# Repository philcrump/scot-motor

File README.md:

# scot-motor

Motor Interface for the SCOT.

* 9-36V DC Input
* STM32F042K6 Microcontroller @ 48MHz
* MCP2562 CAN 2.0A/B Communication Interface
* DRV8872 3.6A PWM H-Bridge Motor Driver
* INA260 Motor Voltage & Current Supply Monitoring
* NCV8450 800mA Clutch Driver
* E-Stop, End-of-travel Limit Interlocks support
  * Hardware CMOS NAND Logic (immune to software override)
  * Opto-isolation of Switches from Logic Inputs (power supply not isolated)

[**Circuit Board Schematic**](https://github.com/philcrump/scot-motor/raw/master/scot-motor-schematic.pdf)

## PCB (CAD Render)

### Errata - April 2020

* ~~0603 footprint used for C3 (4.7uF, 25V), should be 0805 - Minimal impact, 0805 still fits.~~ - Fixed in August 2020.

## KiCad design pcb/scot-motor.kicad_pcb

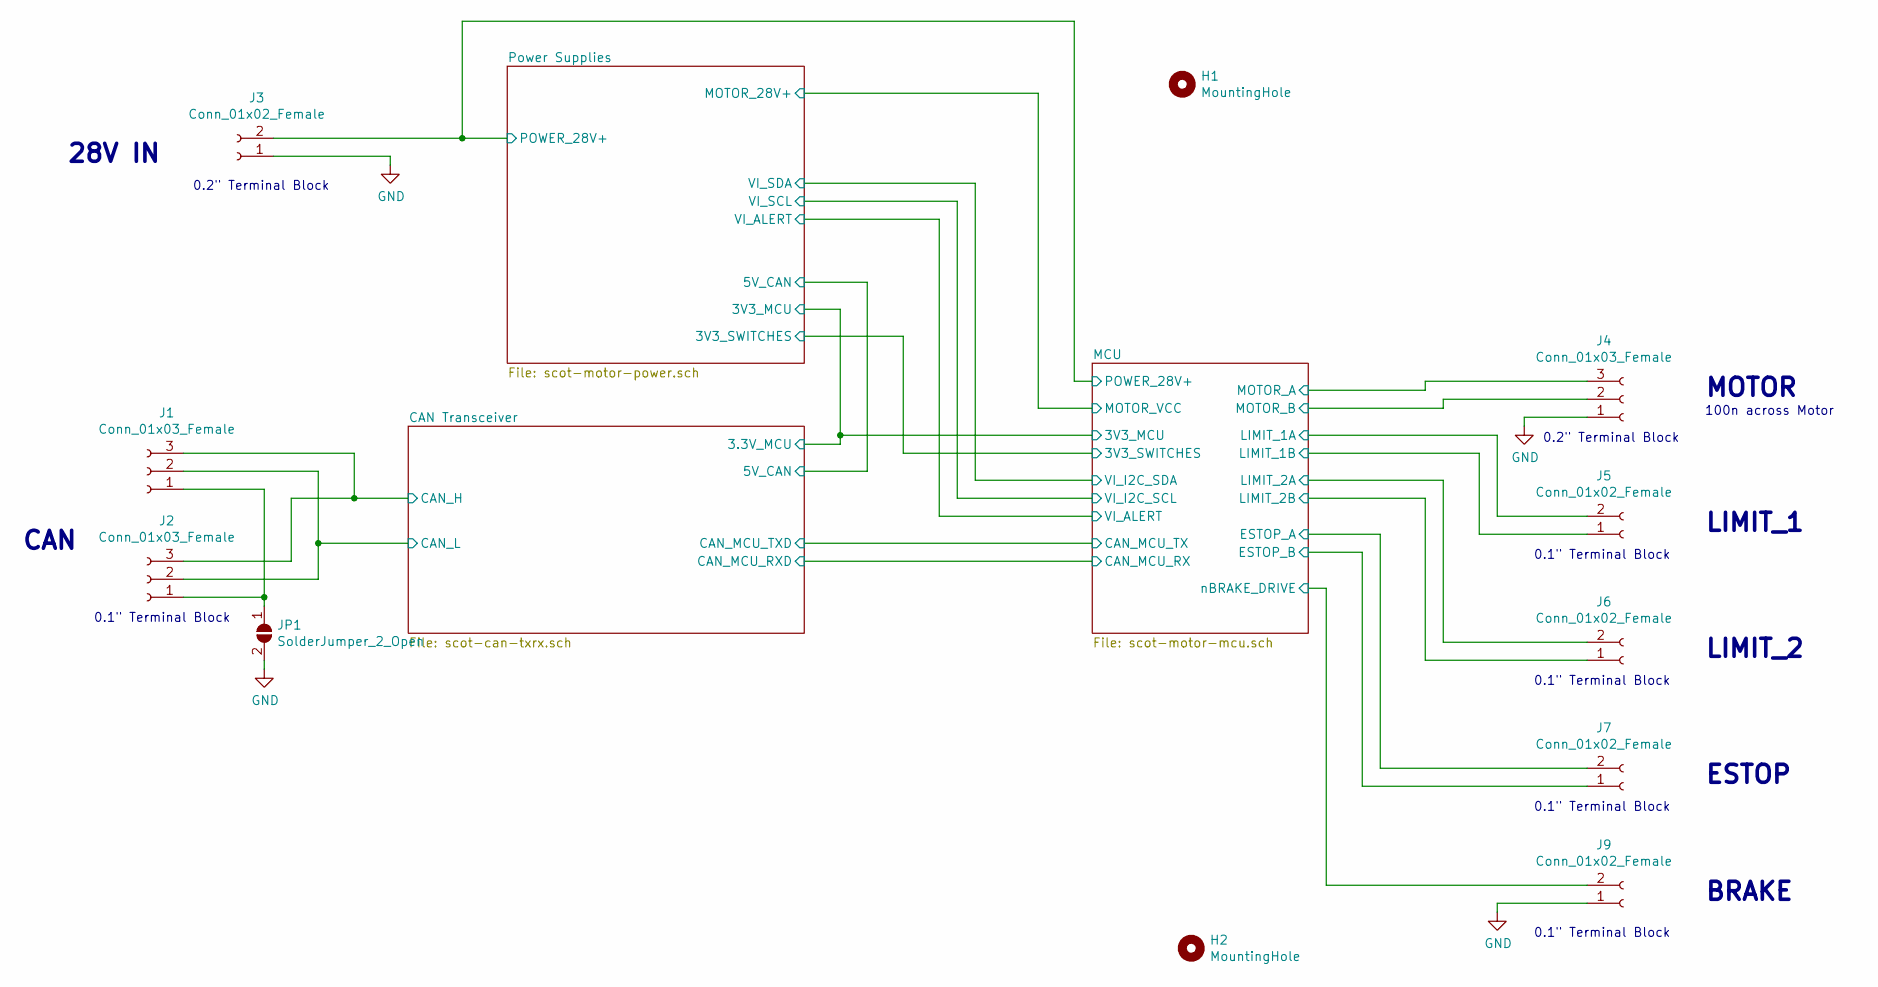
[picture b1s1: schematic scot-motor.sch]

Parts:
H1, H2: MountingHole; M3_MOUNT
J1, J2: Conn_01x03_Female; TerminalBlock_TE_282834-3_1x03_P2.54mm_Horizontal
J3: Conn_01x02_Female; TerminalBlock_RND_205-00287_1x02_P5.08mm_Horizontal
J4: Conn_01x03_Female; TerminalBlock_RND_205-00288_1x03_P5.08mm_Horizontal
J5, J6, J7, J9: Conn_01x02_Female; TerminalBlock_TE_282834-2_1x02_P2.54mm_Horizontal
JP1: SolderJumper_2_Open; SolderJumper-2_P1.3mm_Open_RoundedPad1.0x1.5mm

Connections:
/CAN Transceiver/CAN_H: J1.3, J2.3; also elsewhere on the board
/CAN Transceiver/CAN_L: J1.2, J2.2; also elsewhere on the board
/MCU/ESTOP_A: J7.2; also elsewhere on the board
/MCU/ESTOP_B: J7.1; also elsewhere on the board
/MCU/LIMIT_1A: J5.2; also elsewhere on the board
/MCU/LIMIT_1B: J5.1; also elsewhere on the board
/MCU/LIMIT_2A: J6.2; also elsewhere on the board
/MCU/LIMIT_2B: J6.1; also elsewhere on the board
/MCU/MOTOR_A: J4.3; also elsewhere on the board
/MCU/MOTOR_B: J4.2; also elsewhere on the board
/MCU/POWER_28V+: J3.2; also elsewhere on the board
/MCU/nBRAKE_DRIVE: J9.2; also elsewhere on the board
GND: J3.1, J4.1, J9.1, JP1.2 (B); also elsewhere on the board
unnamed: J1.1, J2.1, JP1.1 (A)

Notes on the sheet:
0.2" Terminal Block
0.1" Terminal Block
MOTOR
LIMIT_1
LIMIT_2
ESTOP
28V IN
CAN
100n across Motor
BRAKE

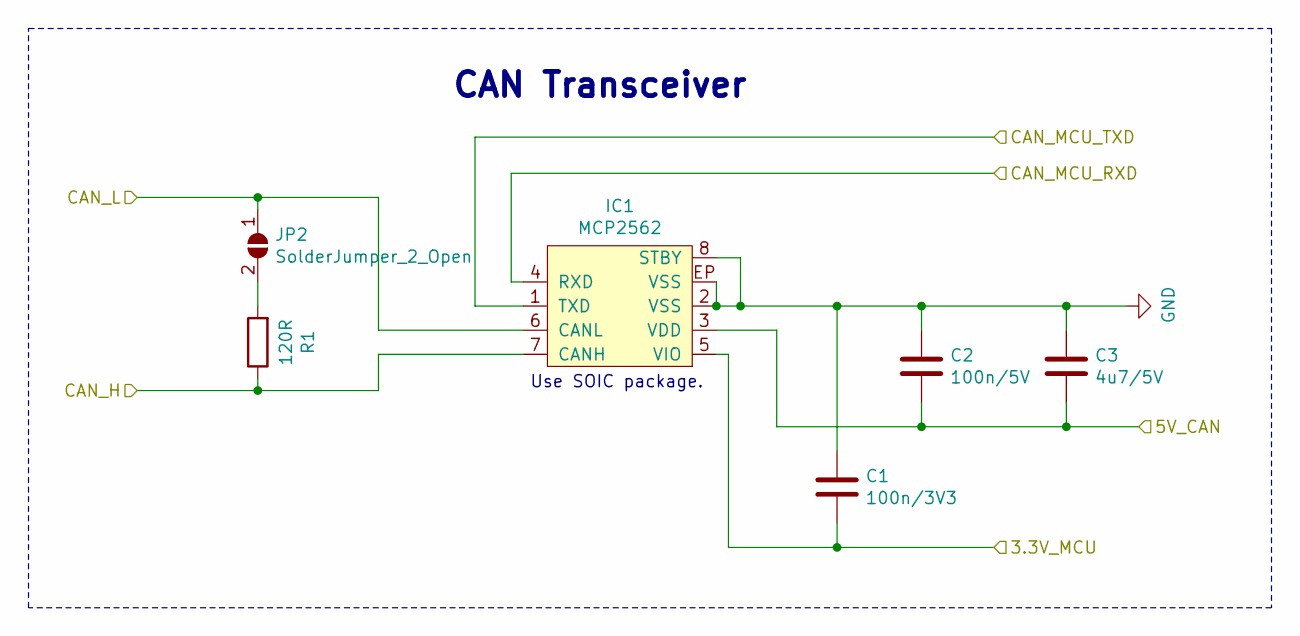
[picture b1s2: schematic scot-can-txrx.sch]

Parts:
C3: 4u7/5V; C_0805_2012Metric_Pad1.15x1.40mm_HandSolder
C53: 100n/3V3; C_0603_1608Metric_Pad1.05x0.95mm_HandSolder
C54: 100n/5V; C_0603_1608Metric_Pad1.05x0.95mm_HandSolder
IC1: MCP2562; SOIC-8-EP
JP2: SolderJumper_2_Open; SolderJumper-2_P1.3mm_Open_RoundedPad1.0x1.5mm
R36: 120R; R_0805_2012Metric_Pad1.15x1.40mm_HandSolder

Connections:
3v3: IC1.5 (VIO); also elsewhere on the board
/CAN Transceiver/5V_CAN: C3.2, IC1.3 (VDD); also elsewhere on the board
/CAN Transceiver/CAN_H: IC1.7 (CANH); also elsewhere on the board
/CAN Transceiver/CAN_L: IC1.6 (CANL), JP2.1 (A); also elsewhere on the board
/MCU/CAN_MCU_RX: IC1.4 (RXD); also elsewhere on the board
/MCU/CAN_MCU_TX: IC1.1 (TXD); also elsewhere on the board
GND: C3.1, IC1.2 (VSS), IC1.8 (STBY), IC1.EP (VSS); also elsewhere on the board
unnamed 57: JP2.2 (B); also elsewhere on the board

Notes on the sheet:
Use SOIC package.
CAN Transceiver

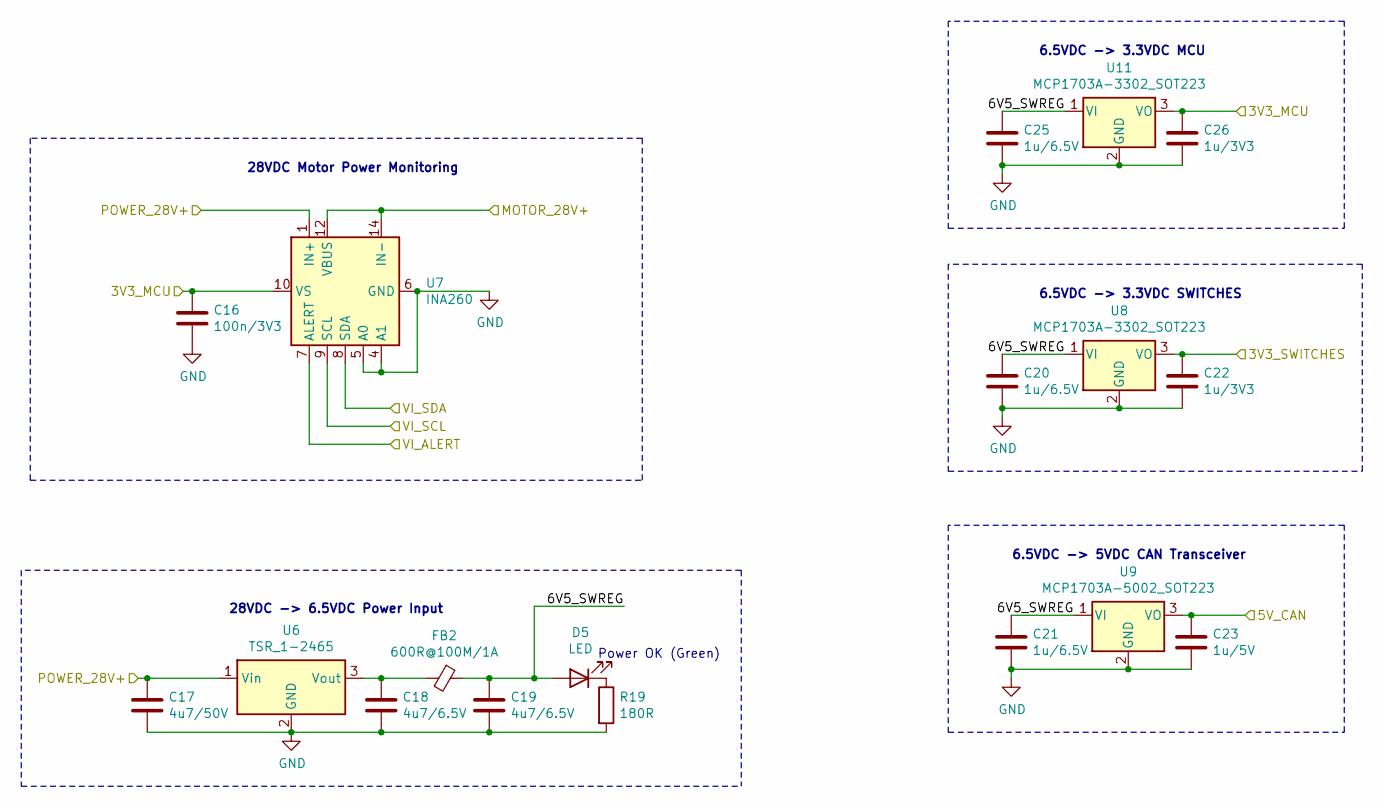
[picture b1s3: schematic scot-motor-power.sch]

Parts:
C16: 100n/3V3; C_0603_1608Metric_Pad1.05x0.95mm_HandSolder
C17: 4u7/50V; C_1206_3216Metric_Pad1.42x1.75mm_HandSolder
C18, C19: 4u7/6.5V; C_0805_2012Metric_Pad1.15x1.40mm_HandSolder
C20, C21, C25: 1u/6.5V; C_0603_1608Metric_Pad1.05x0.95mm_HandSolder
C22, C26: 1u/3V3; C_0603_1608Metric_Pad1.05x0.95mm_HandSolder
C23: 1u/5V; C_0603_1608Metric_Pad1.05x0.95mm_HandSolder
D5: LED; LED_1210_3225Metric_Pad1.42x2.65mm_HandSolder
FB2: 600R@100M/1A; L_0805_2012Metric_Pad1.15x1.40mm_HandSolder
R19: 180R; R_0805_2012Metric_Pad1.15x1.40mm_HandSolder
U6: TSR_1-2465; Converter_DCDC_TRACO_TSR-1_THT
U7: INA260; TSSOP-16_4.4x5mm_P0.65mm
U8, U11: MCP1703A-3302_SOT223; SOT-223-3_TabPin2
U9: MCP1703A-5002_SOT223; SOT-223-3_TabPin2

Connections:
3v3: C16.1, C26.1, U7.10 (VS), U11.3 (VO); also elsewhere on the board
+3.3VP: C22.1, U8.3 (VO); also elsewhere on the board
/CAN Transceiver/5V_CAN: C23.1, U9.3 (VO); also elsewhere on the board
/MCU/POWER_28V+: C17.1, U6.1 (Vin), U7.1 (IN+), U7.2 (IN+), U7.3 (IN+); also elsewhere on the board
/MCU/VI_ALERT: U7.7 (ALERT); also elsewhere on the board
/MCU/VI_I2C_SCL: U7.9 (SCL); also elsewhere on the board
/MCU/VI_I2C_SDA: U7.8 (SDA); also elsewhere on the board
/Power Supplies/6V5_SWREG: C19.1, C20.1, C21.1, C25.1, D5.2 (A), FB2.1, U8.1 (VI), U9.1 (VI), U11.1 (VI)
/Power Supplies/MOTOR_28V+: U7.12 (VBUS), U7.14 (IN-), U7.15 (IN-), U7.16 (IN-); also elsewhere on the board
GND: C16.2, C17.2, C18.2, C19.2, C20.2, C21.2, C22.2, C23.2, C25.2, C26.2, R19.2, U6.2 (GND), U7.4 (A1), U7.5 (A0), U7.6 (GND), U7.11 (GND), U8.2 (GND), U9.2 (GND), U11.2 (GND); also elsewhere on the board
unnamed: C18.1, FB2.2, U6.3 (Vout)
unnamed: D5.1 (K), R19.1

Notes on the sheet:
6.5VDC -> 5VDC CAN Transceiver
6.5VDC -> 3.3VDC SWITCHES
28VDC -> 6.5VDC Power Input
28VDC Motor Power Monitoring
Power OK (Green)
6.5VDC -> 3.3VDC MCU

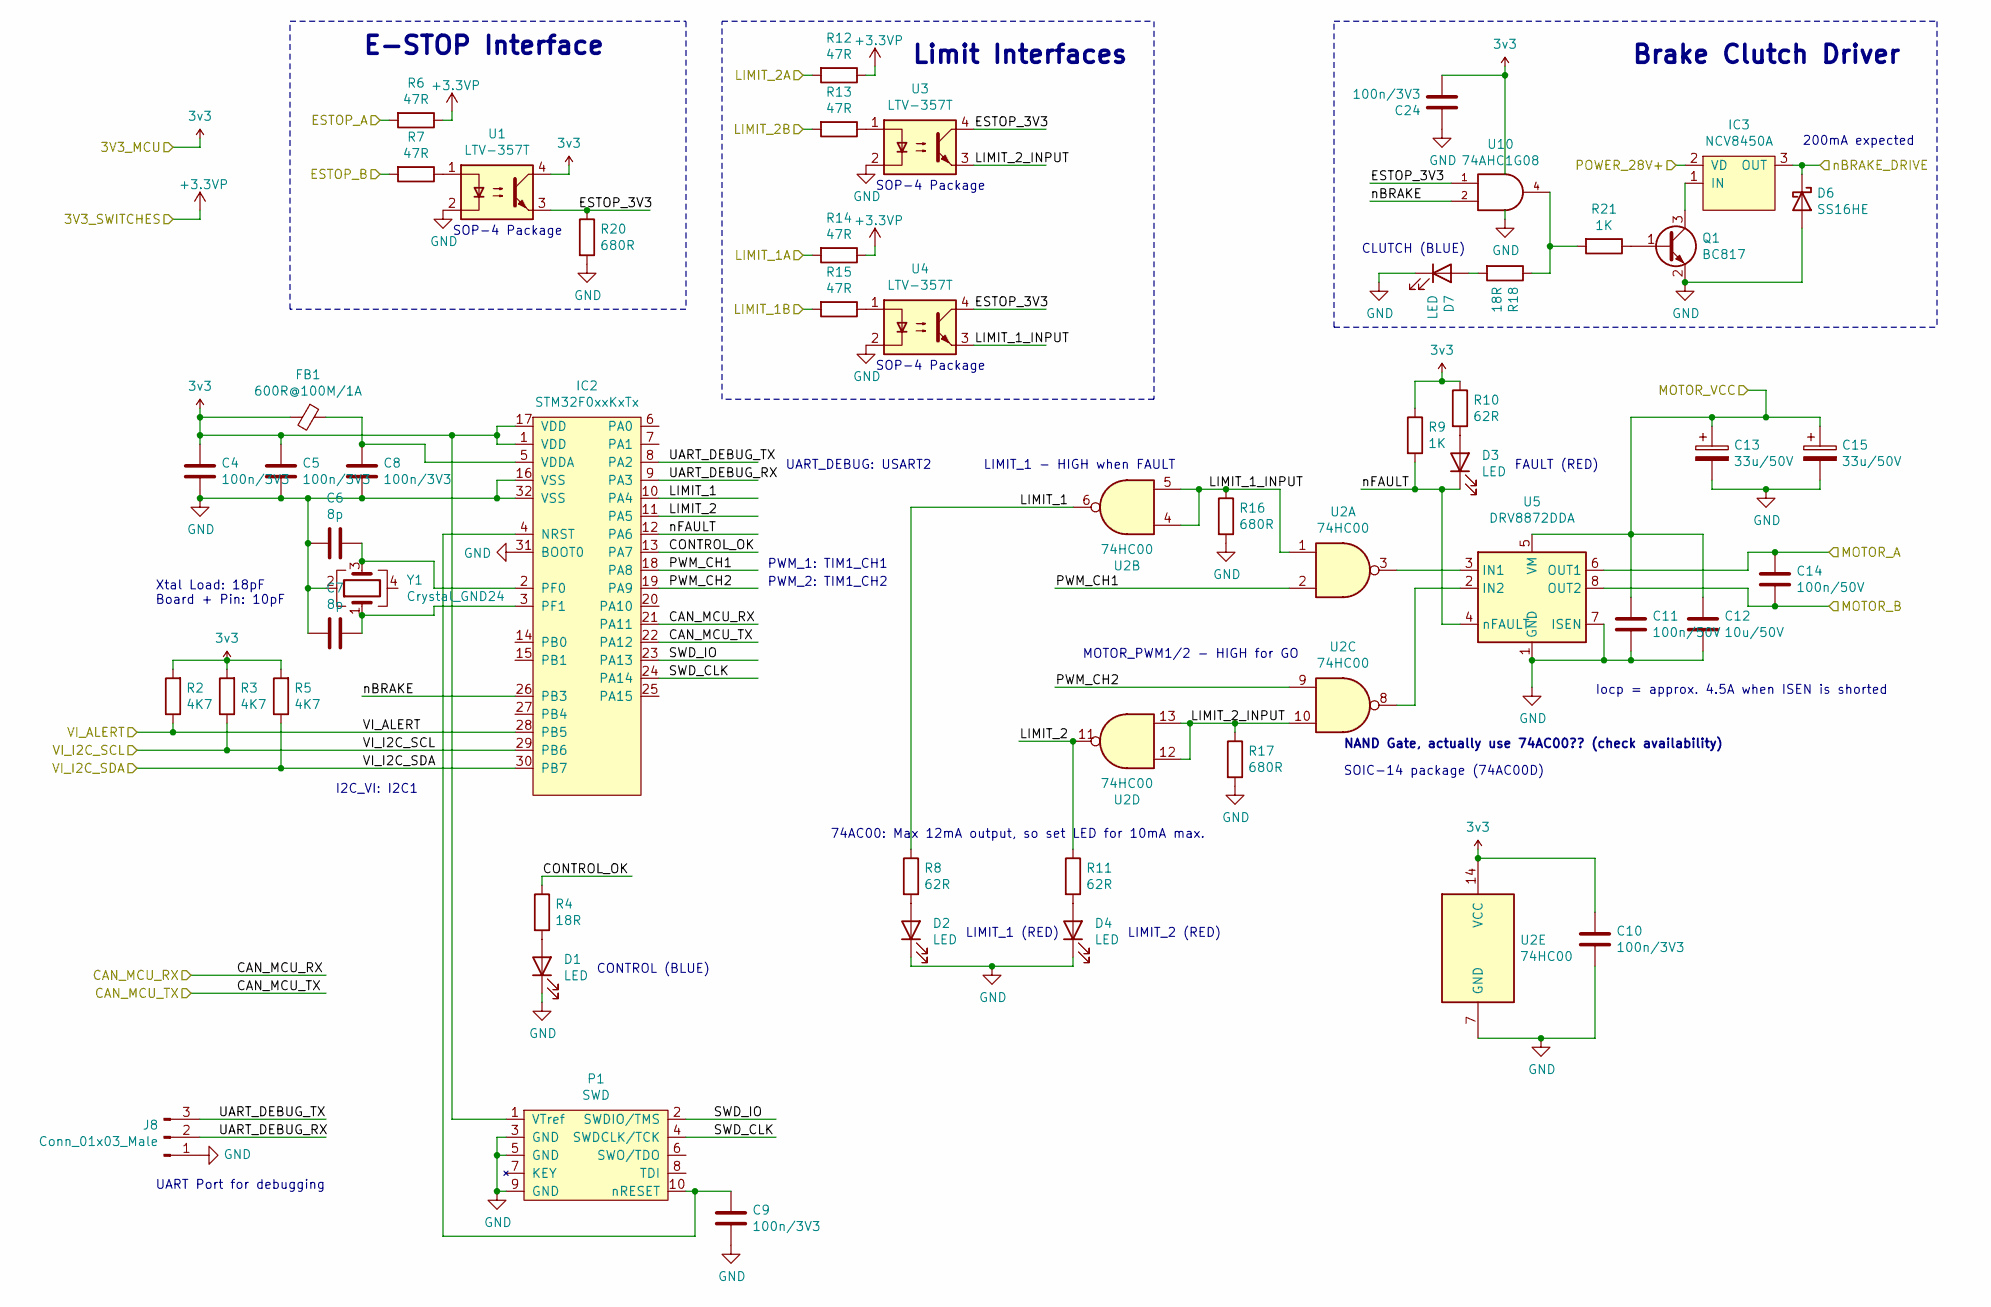
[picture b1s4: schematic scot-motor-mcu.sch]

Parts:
C4, C5, C8, C9, C10, C24: 100n/3V3; C_0603_1608Metric_Pad1.05x0.95mm_HandSolder
C6, C7: 8p; C_0603_1608Metric_Pad1.05x0.95mm_HandSolder
C11, C14: 100n/50V; C_0603_1608Metric_Pad1.05x0.95mm_HandSolder
C12: 10u/50V; C_1210_3225Metric_Pad1.42x2.65mm_HandSolder
C13, C15: 33u/50V; CP_Elec_8x10.5
D1, D2, D3, D4, D7: LED; LED_1210_3225Metric_Pad1.42x2.65mm_HandSolder
D6: SS16HE; SOD-323
FB1: 600R@100M/1A; L_0805_2012Metric_Pad1.15x1.40mm_HandSolder
IC2: STM32F0xxKxTx; LQFP-32; Farnell 2432085
IC3: NCV8450A; SOT-223-3_TabPin2; Mouser 863-NCV8450ASTT3G
J8: Conn_01x03_Male; PinHeader_1x03_P2.54mm_Vertical
P1: SWD; FTSH-105-01-F-D-K
Q1: BC817; SOT-23
R2, R3, R5: 4K7; R_0603_1608Metric_Pad1.05x0.95mm_HandSolder
R4, R18: 18R; R_0805_2012Metric_Pad1.15x1.40mm_HandSolder
R6, R7, R12, R13, R14, R15: 47R; R_0805_2012Metric_Pad1.15x1.40mm_HandSolder
R8, R10, R11: 62R; R_0805_2012Metric_Pad1.15x1.40mm_HandSolder
R9, R21: 1K; R_0603_1608Metric_Pad1.05x0.95mm_HandSolder
R16, R17, R20: 680R; R_0603_1608Metric_Pad1.05x0.95mm_HandSolder
U1, U3, U4: LTV-357T; SO-4_4.4x3.6mm_P2.54mm
U2: 74HC00; SOIC-14
U5: DRV8872DDA; Texas_HTSOP-8-1EP_3.9x4.9mm_P1.27mm_EP2.95x4.9mm_Mask2.4x3.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
U10: 74AHC1G08; SOT-23-5
Y1: Crystal_GND24; Crystal_SMD_Abracon_ABM8G-4Pin_3.2x2.5mm

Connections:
3v3: C4.1, C5.1, C10.1, C24.2, FB1.2, IC2.1 (VDD), IC2.17 (VDD), P1.1 (VTref), R2.2, R3.2, R5.2, R9.1, R10.1, U1.4, U2.14 (VCC), U10.5 (VCC); also elsewhere on the board
+3.3VP: R6.1, R12.1, R14.1; also elsewhere on the board
/MCU/CAN_MCU_RX: IC2.21 (PA11); also elsewhere on the board
/MCU/CAN_MCU_TX: IC2.22 (PA12); also elsewhere on the board
/MCU/CONTROL_OK: IC2.13 (PA7), R4.1
/MCU/ESTOP_3V3: R20.1, U1.3, U3.4, U4.4, U10.1
/MCU/ESTOP_A: R6.2; also elsewhere on the board
/MCU/ESTOP_B: R7.2; also elsewhere on the board
/MCU/LIMIT_1: IC2.10 (PA4), R8.1, U2.6
/MCU/LIMIT_1A: R14.2; also elsewhere on the board
/MCU/LIMIT_1B: R15.2; also elsewhere on the board
/MCU/LIMIT_1_INPUT: R16.1, U2.1, U2.4, U2.5, U4.3
/MCU/LIMIT_2: IC2.11 (PA5), R11.1, U2.11
/MCU/LIMIT_2A: R12.2; also elsewhere on the board
/MCU/LIMIT_2B: R13.2; also elsewhere on the board
/MCU/LIMIT_2_INPUT: R17.1, U2.10, U2.12, U2.13, U3.3
/MCU/MOTOR_A: C14.1, U5.6 (OUT1); also elsewhere on the board
/MCU/MOTOR_B: C14.2, U5.8 (OUT2); also elsewhere on the board
/MCU/POWER_28V+: IC3.2 (VD); also elsewhere on the board
/MCU/PWM_CH1: IC2.18 (PA8), U2.2
/MCU/PWM_CH2: IC2.19 (PA9), U2.9
/MCU/SWD_CLK: IC2.24 (PA14), P1.4 (SWDCLK/TCK)
/MCU/SWD_IO: IC2.23 (PA13), P1.2 (SWDIO/TMS)
/MCU/UART_DEBUG_RX: IC2.9 (PA3), J8.2
/MCU/UART_DEBUG_TX: IC2.8 (PA2), J8.3
/MCU/VI_ALERT: IC2.28 (PB5), R2.1; also elsewhere on the board
/MCU/VI_I2C_SCL: IC2.29 (PB6), R3.1; also elsewhere on the board
/MCU/VI_I2C_SDA: IC2.30 (PB7), R5.1; also elsewhere on the board
/MCU/nBRAKE: IC2.26 (PB3), U10.2
/MCU/nBRAKE_DRIVE: D6.1 (K), IC3.3 (OUT); also elsewhere on the board
/MCU/nFAULT: D3.1 (K), IC2.12 (PA6), R9.2, U5.4 (nFAULT)
/Power Supplies/MOTOR_28V+: C11.1, C12.1, C13.1, C15.1, U5.5 (VM); also elsewhere on the board
GND: C4.2, C5.2, C6.2, C7.2, C8.2, C9.2, C10.2, C11.2, C12.2, C13.2, C15.2, C24.1, D1.1 (K), D2.1 (K), D4.1 (K), D6.2 (A), D7.1 (K), IC2.16 (VSS), IC2.31 (BOOT0), IC2.32 (VSS), J8.1, P1.3 (GND), P1.5 (GND), P1.9 (GND), Q1.2 (E), R16.2, R17.2, R20.2, U1.2, U2.7 (GND), U3.2, U4.2, U5.1 (GND), U5.7 (ISEN), U5.9 (GND), U10.3 (GND), Y1.2; also elsewhere on the board
unnamed: C6.1, IC2.2 (PF0), Y1.3
unnamed: C7.1, IC2.3 (PF1), Y1.1
unnamed: C8.1, FB1.1, IC2.5 (VDDA)
unnamed: C9.1, IC2.4 (NRST), P1.10 (nRESET)
unnamed: D1.2 (A), R4.2
unnamed: D2.2 (A), R8.2
unnamed: D3.2 (A), R10.2
unnamed: D4.2 (A), R11.2
unnamed: D7.2 (A), R18.2
unnamed: IC3.1 (IN), Q1.3 (C)
unnamed: Q1.1 (B), R21.1
unnamed: R7.1, U1.1
unnamed: R13.1, U3.1
unnamed: R15.1, U4.1
unnamed: R18.1, R21.2, U10.4
unnamed: U2.3, U5.3 (IN1)
unnamed: U2.8, U5.2 (IN2)

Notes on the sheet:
Iocp = approx. 4.5A when ISEN is shorted
LIMIT_1 - HIGH when FAULT
MOTOR_PWM1/2 - HIGH for GO
NAND Gate, actually use 74AC00?? (check availability)
FAULT (RED)
LIMIT_2 (RED)
LIMIT_1 (RED)
UART Port for debugging
CONTROL (BLUE)
SOP-4 Package
I2C_VI: I2C1
UART_DEBUG: USART2
PWM_1: TIM1_CH1
PWM_2: TIM1_CH2
74AC00: Max 12mA output, so set LED for 10mA max.
SOIC-14 package (74AC00D)
200mA expected
E-STOP Interface
Brake Clutch Driver
Limit Interfaces
CLUTCH (BLUE)
Xtal Load: 18pF Board + Pin: 10pF

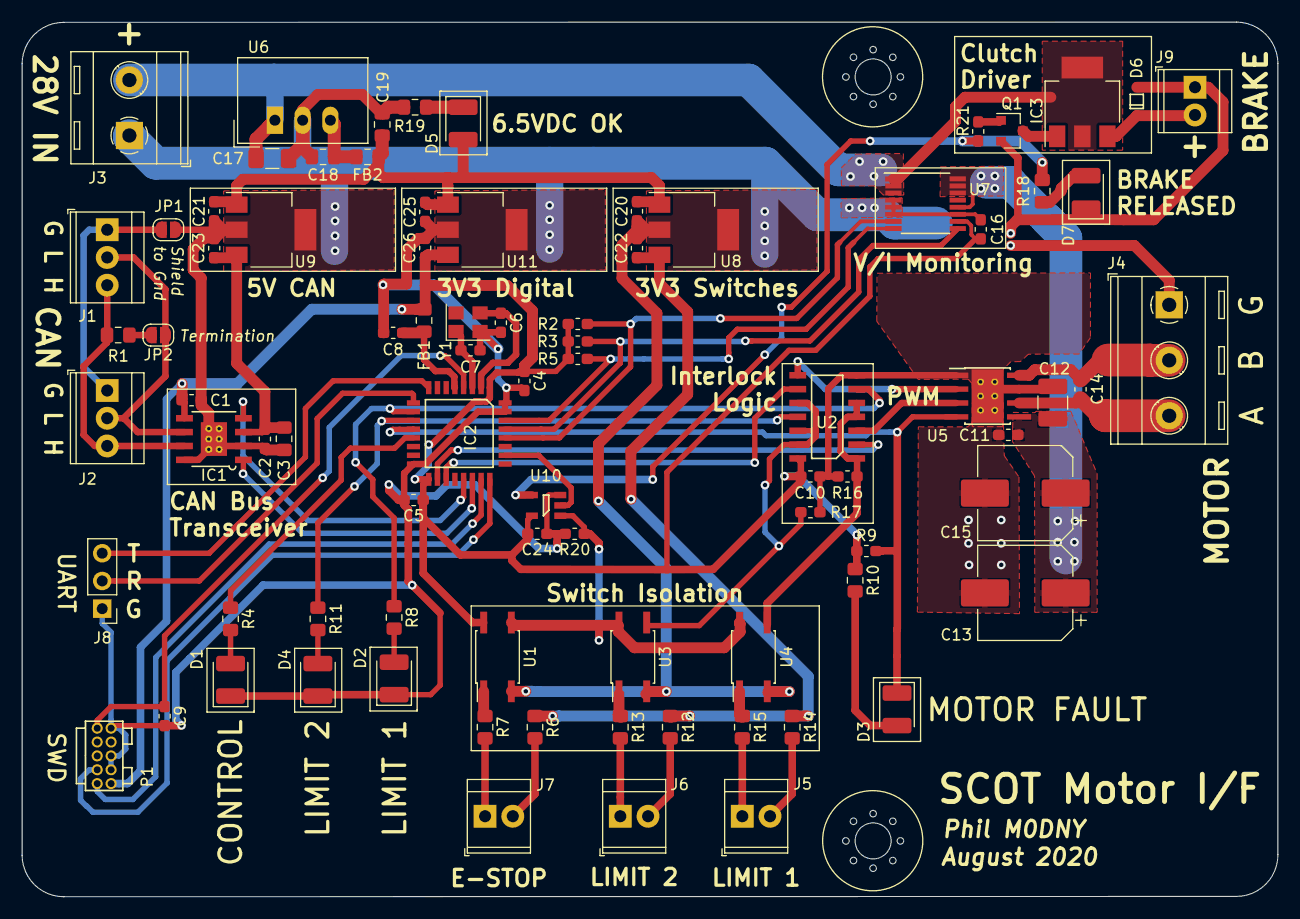
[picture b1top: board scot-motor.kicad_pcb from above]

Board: 2 copper layers, 115.1 x 80.1 mm, 86 parts (0 on the bottom side), 58 nets.

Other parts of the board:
C1: 100n/3V3; C_0603_1608Metric_Pad1.05x0.95mm_HandSolder
C2: 100n/5V; C_0603_1608Metric_Pad1.05x0.95mm_HandSolder
R1: 120R; R_0805_2012Metric_Pad1.15x1.40mm_HandSolder

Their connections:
3v3: C1.2; also elsewhere on the board
/CAN Transceiver/5V_CAN: C2.2; also elsewhere on the board
/CAN Transceiver/CAN_H: R1.1; also elsewhere on the board
GND: C1.1, C2.1; also elsewhere on the board
unnamed 57: R1.2; also elsewhere on the board

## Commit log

2020-02-25 Initial commit.
2020-04-04 WIP.
2020-04-05 Add schematic.
2020-04-05 pcb: Add brake clutch driver.
2020-04-06 pcb: Link brake clutch to e-stop, aesthetic tweaks.
2020-04-11 PCB progress, schematic fixes.
2020-04-16 PCB progress.
2020-04-18 pcb: Add ground terminal on motor terminal block for shielding.
2020-04-18 pcb: Add Clutch Release indicator.
2020-04-18 pcb: Final tweaks.
2020-04-18 pcb: Fix some DRC warnings, produce gerbers for cam.
2020-04-18 README: Add detail.
2020-04-18 README: Add INA260.
2020-04-19 pcb: Add BOM list. Adjust some values to reduce lines.
2020-04-20 pcb: Fix MCU xtal load capacitors.
2020-05-10 firmware: Standalone working.
2020-05-13 firmware: Add start of CAN comms.
2020-05-14 firmware: Improvements, ready for integration.
2020-05-31 firmware/Chibi: Update ref.
2020-05-31 travis: Update to 2020 Q2 compiler.
2020-06-05 pcb/BOM: Use same 100n as other projects.
2020-06-05 firmware/ChibiOS: Update ref.
2020-06-08 firmware/Makefile: Enable GCC version check now Chibi bug #985 fixed.
2020-07-25 firmware/: Update Chibios ref.
2020-07-25 firmware/: Load CAN addresses from STM32 ID lookup, add both board STM32 IDs.
2020-08-09 pcb/: Fixi C3 footprint and re-plot.
